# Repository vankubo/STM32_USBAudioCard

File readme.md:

# STM32F411 USB声卡

* PCB编辑器：KiCAD
* 固件开发：Keil

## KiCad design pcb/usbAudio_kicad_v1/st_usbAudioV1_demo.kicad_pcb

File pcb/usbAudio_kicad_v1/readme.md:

## 2021.5

* 初版验证成功

## 2021.6.3

### 第二版

* 增加TPA6138A2耳放
* 电位器封装使用贴片
* 修改USB封装

* 修改LCD为焊接式
* 增加背光控制电路
* 修改耳机孔为直插式

* 电压输入滤波计划更换为钽电容

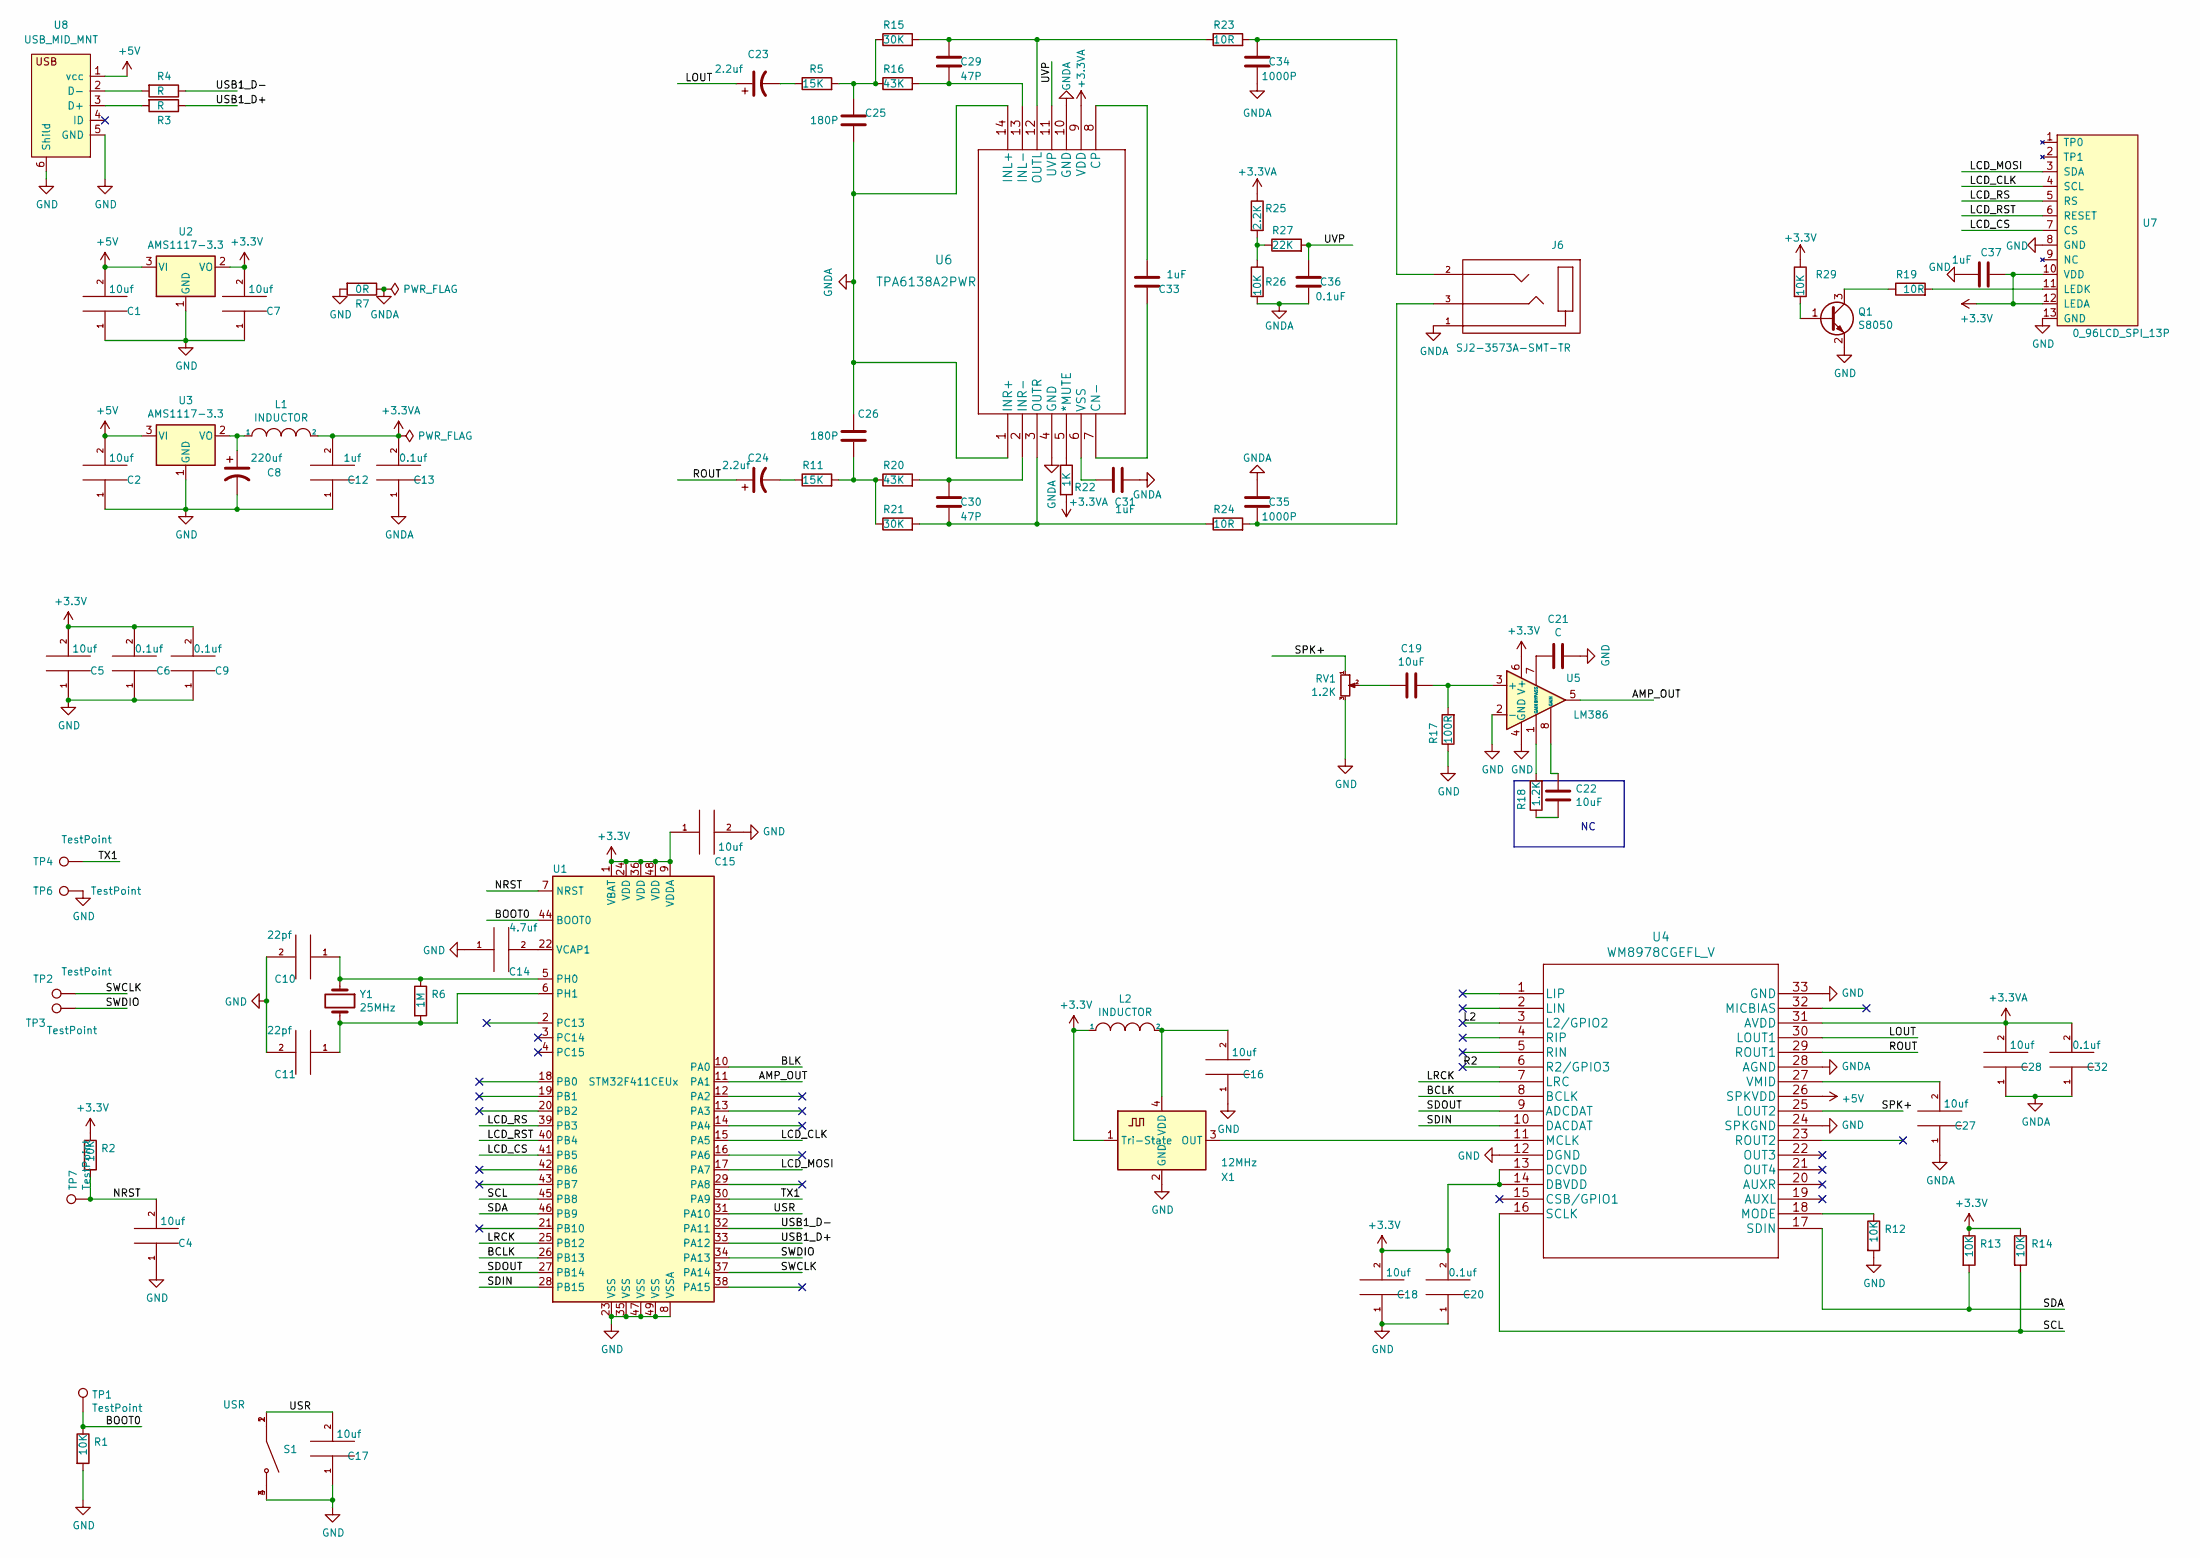
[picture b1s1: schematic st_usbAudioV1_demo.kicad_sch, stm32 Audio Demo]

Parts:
C1, C2, C4, C5, C7, C15, C16, C17, C18, C27, C28: 10uf; C_0805_2012Metric
C6, C9, C13, C20, C32: 0.1uf; C_0805_2012Metric
C8: 220uf; TAJD107M016RNJ7343
C10, C11: 22pf; C_0805_2012Metric
C12: 1uf; C_0805_2012Metric
C14: 4.7uf; C_0805_2012Metric
C19, C22: 10uF; C_0805_2012Metric
C21: C; C_0805_2012Metric
C23, C24: 2.2uf; TAJD107M016RNJ7343
C25, C26: 180P; C_0805_2012Metric
C29, C30: 47P; C_0805_2012Metric
C31, C33, C37: 1uF; C_0805_2012Metric
C34, C35: 1000P; C_0805_2012Metric
C36: 0.1uF; C_0805_2012Metric
J6: SJ2-3573A-SMT-TR; PJ-313D; PART_REV 1.01
L1: INDUCTOR; L_TDK_NLV32_3.2x2.5mm
L2: INDUCTOR; L_0805_2012Metric
Q1: S8050; SOT-23
R1, R2, R12, R13, R14, R26, R29: 10K; R_0603_1608Metric
R3, R4: R; R_0603_1608Metric
R5, R11: 15K; R_0603_1608Metric
R6: 1M; R_0603_1608Metric
R7: 0R; R_0603_1608Metric
R15, R21: 30K; R_0603_1608Metric
R16, R20: 43K; R_0603_1608Metric
R17: 100R; R_0603_1608Metric
R18: 1.2K; R_0603_1608Metric
R19, R23, R24: 10R; R_0603_1608Metric
R22: 1K; R_0603_1608Metric
R25: 2.2K; R_0603_1608Metric
R27: 22K; R_0603_1608Metric
RV1: 1.2K; Potentiometer_Bourns_TC33X_Vertical
S1: USR; SKQGAKE010
TP1, TP2, TP3, TP4, TP6, TP7: TestPoint; TestPoint_Pad_1.0x1.0mm
U1: STM32F411CEUx; QFN-48-1EP_7x7mm_P0.5mm_EP5.6x5.6mm
U2, U3: AMS1117-3.3; SOT-223-3_TabPin2
U4: WM8978CGEFL_V; WM8978CGEFL
U5: LM386; HSOP-8-1EP_3.9x4.9mm_P1.27mm_EP2.41x3.1mm
U6: TPA6138A2PWR
U7: 0_96LCD_SPI_13P
U8: USB_MID_MNT; MICRO-USB-SMD_MICRO-5P-P0.8_1
X1: 12MHz; Crystal_SMD_3225-4Pin_3.2x2.5mm
Y1: 25MHz; Crystal_SMD_5032-2Pin_5.0x3.2mm

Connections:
+3.3VA: C12.2, C13.2, C28.2, C32.2, L1.2, R22.2, R25.1, U4.31 (AVDD), U6.9 (VDD)
+3V3: C5.2, C6.2, C7.2, C9.2, C15.1, C18.2, C20.2, C37.2, L2.1, R2.1, R13.1, R14.1, R29.1, U1.1 (VBAT), U1.9 (VDDA), U1.24 (VDD), U1.36 (VDD), U1.48 (VDD), U2.2 (VO), U4.13 (DCVDD), U4.14 (DBVDD), U5.6 (V+), U7.10 (VDD), U7.12 (LEDA), X1.1 (Tri-State)
+5V: C1.2, C2.2, U2.3 (VI), U3.3 (VI), U4.26 (SPKVDD), U8.1 (vcc)
/AMP_OUT: U1.11 (PA1), U5.5
/BCLK: U1.26 (PB13), U4.8 (BCLK)
/BLK: U1.10 (PA0)
/BOOT0: R1.1, TP1.1, U1.44 (BOOT0)
/L2: U4.3 (L2/GPIO2)
/LCD_CLK: U1.15 (PA5), U7.4 (SCL)
/LCD_CS: U1.41 (PB5), U7.7 (CS)
/LCD_MOSI: U1.17 (PA7), U7.3 (SDA)
/LCD_RS: U1.39 (PB3), U7.5 (RS)
/LCD_RST: U1.40 (PB4), U7.6 (RESET)
/LOUT: C23.1, U4.30 (LOUT1)
/LRCK: U1.25 (PB12), U4.7 (LRC)
/NRST: C4.2, R2.2, TP7.1, U1.7 (NRST)
/R2: U4.6 (R2/GPIO3)
/ROUT: C24.1, U4.29 (ROUT1)
/SCL: R14.2, U1.45 (PB8), U4.16 (SCLK)
/SDA: R13.2, U1.46 (PB9), U4.17 (SDIN)
/SDIN: U1.28 (PB15), U4.10 (DACDAT)
/SDOUT: U1.27 (PB14), U4.9 (ADCDAT)
/SPK+: RV1.1, U4.25 (LOUT2)
/SWCLK: TP2.1, U1.37 (PA14)
/SWDIO: TP3.1, U1.34 (PA13)
/TX1: TP4.1, U1.30 (PA9)
/USB1_D+: R3.1, U1.33 (PA12)
/USB1_D-: R4.1, U1.32 (PA11)
/USR: C17.2, S1.1, S1.2, U1.31 (PA10)
/UVP: C36.1, R27.2, U6.11 (UVP)
GND: C1.1, C2.1, C4.1, C5.1, C6.1, C7.1, C8.2, C9.1, C10.2, C11.2, C12.1, C14.1, C15.2, C16.1, C17.1, C18.1, C20.1, C21.1, C37.1, Q1.2 (E), R1.2, R7.2, R12.2, R17.1, RV1.3, S1.3, S1.4, TP6.1, U1.8 (VSSA), U1.23 (VSS), U1.35 (VSS), U1.47 (VSS), U1.49 (VSS), U2.1 (GND), U3.1 (GND), U4.12 (DGND), U4.24 (SPKGND), U4.33 (GND), U5.2 (-), U5.4 (GND), U7.8 (GND), U7.13 (GND), U8.5 (GND), U8.6 (Shild), X1.2 (GND)
GNDA: C13.1, C25.2, C26.1, C27.1, C28.1, C31.1, C32.1, C34.2, C35.1, C36.2, J6.1, R7.1, R26.2, U4.28 (AGND), U6.1 (INR+), U6.4 (GND), U6.10 (GND), U6.14 (INL+)
unnamed: C8.1, L1.1, U3.2 (VO)
unnamed: C10.1, R6.1, U1.5 (PH0), Y1.1
unnamed: C11.1, R6.2, U1.6 (PH1), Y1.2
unnamed: C14.2, U1.22 (VCAP1)
unnamed: C16.2, L2.2, X1.4 (VDD)
unnamed: C19.1, R17.2, U5.3 (+)
unnamed: C19.2, RV1.2
unnamed: C21.2, U5.7 (BYPASS)
unnamed: C22.1, U5.8 (GAIN)
unnamed: C22.2, R18.1
unnamed: C23.2, R5.1
unnamed: C24.2, R11.1
unnamed: C25.1, R5.2, R15.1, R16.1
unnamed: C26.2, R11.2, R20.1, R21.1
unnamed: C27.2, U4.27 (VMID)
unnamed: C29.1, R15.2, R23.1, U6.12 (OUTL)
unnamed: C29.2, R16.2, U6.13 (INL-)
unnamed: C30.1, R20.2, U6.2 (INR-)
unnamed: C30.2, R21.2, R24.1, U6.3 (OUTR)
unnamed: C31.2, U6.6 (VSS)
unnamed: C33.1, U6.8 (CP)
unnamed: C33.2, U6.7 (CN-)
unnamed: C34.1, J6.2, R23.2
unnamed: C35.2, J6.3, R24.2
unnamed: Q1.1 (B), R29.2
unnamed: Q1.3 (C), R19.1
unnamed: R3.2, U8.3 (D+)
unnamed: R4.2, U8.2 (D-)
unnamed: R12.1, U4.18 (MODE)
unnamed: R18.2, U5.1 (GAIN)
unnamed: R19.2, U7.11 (LEDK)
unnamed: R22.1, U6.5 (*MUTE)
unnamed: R25.2, R26.1, R27.1
unnamed: U4.11 (MCLK), X1.3 (OUT)

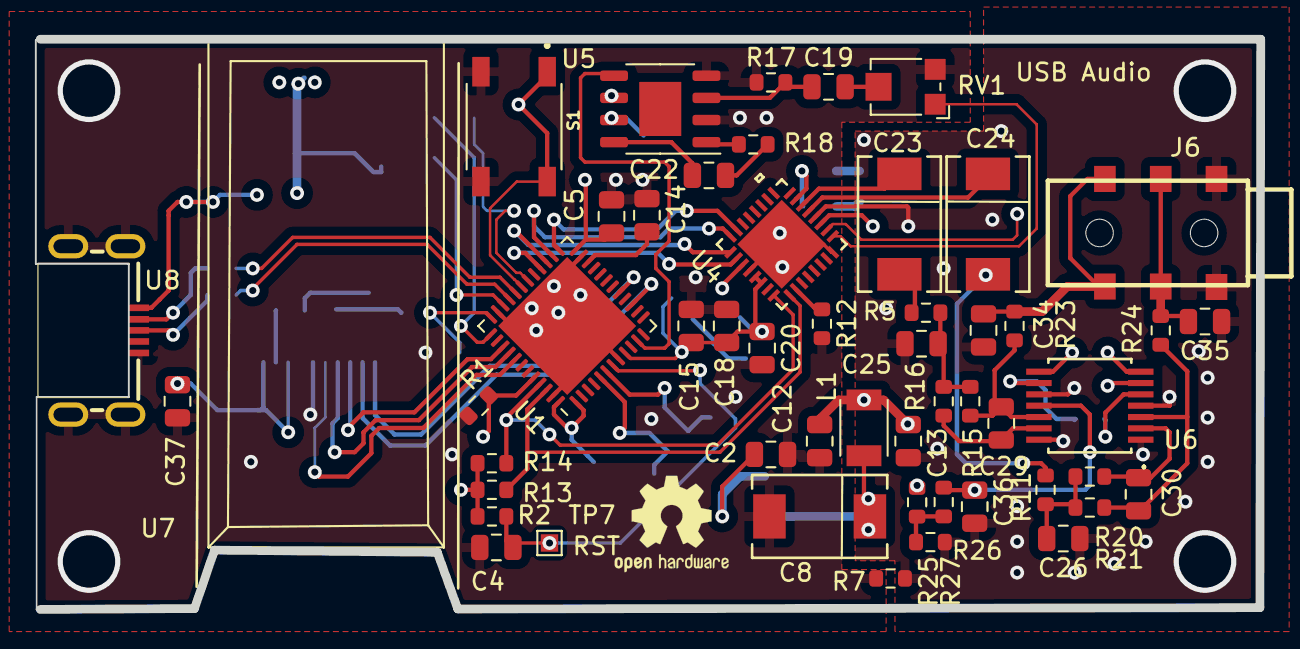
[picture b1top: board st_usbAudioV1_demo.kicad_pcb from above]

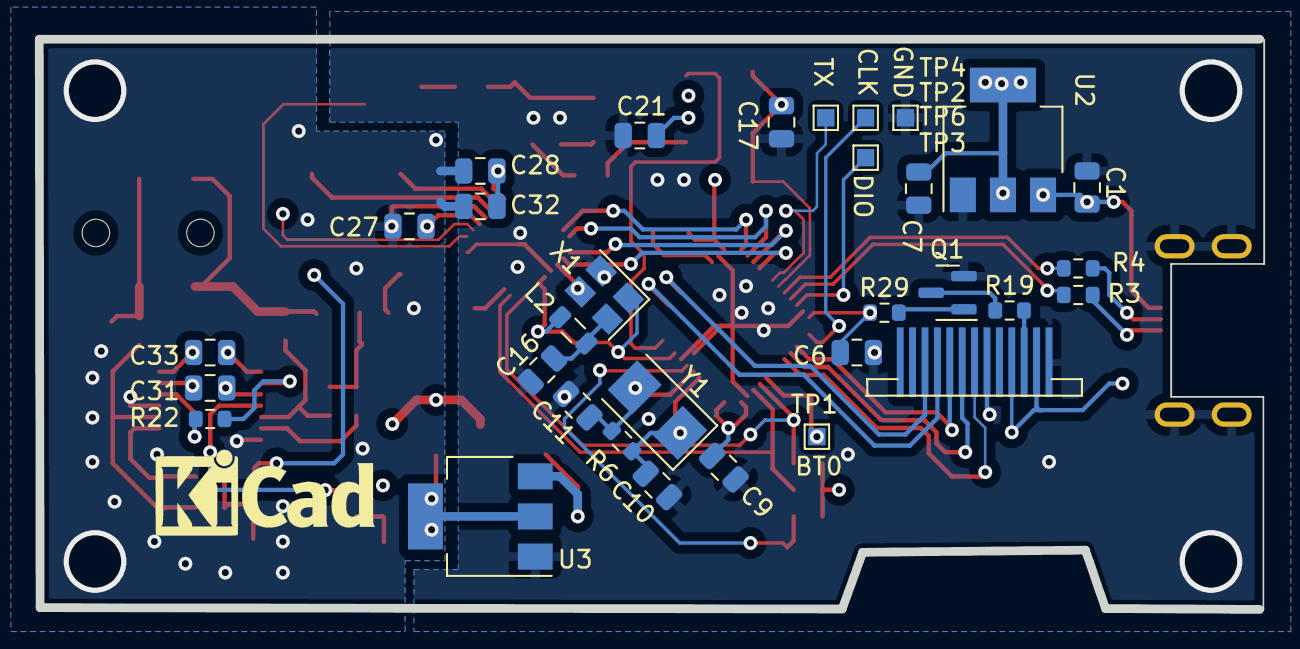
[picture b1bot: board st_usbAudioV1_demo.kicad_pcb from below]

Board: 4 copper layers, 70.1 x 32.7 mm, 83 parts (31 on the bottom side), 63 nets.

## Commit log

2022-03-26 version2

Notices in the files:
parts and their libraries:
Copyright 2016 Accelerated Designs. All rights reserved.
